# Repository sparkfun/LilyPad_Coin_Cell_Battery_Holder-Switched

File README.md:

SparkFun LilyPad Coin Cell Battery Holder-Switched
========================================

[*SparkFun LilyPad Coin Cell Battery Holder-Switched (DEV-11285)*](https://www.sparkfun.com/products/11285)

This LilyPad Coin Cell Battery Holder has a small slide switch installed on the board, 
in-line with the power so you can shut off your project and save batteries.

Repository Contents
-------------------
* **/Hardware** - All Eagle design files (.brd, .sch)

License Information
-------------------
The hardware is released under [Creative Commons ShareAlike 4.0 International](https://creativecommons.org/licenses/by-sa/4.0/).
Note: A portion of this sale is given back to Dr. Leah Buechley for continued development and education of e-textiles.

Distributed as-is; no warranty is given.

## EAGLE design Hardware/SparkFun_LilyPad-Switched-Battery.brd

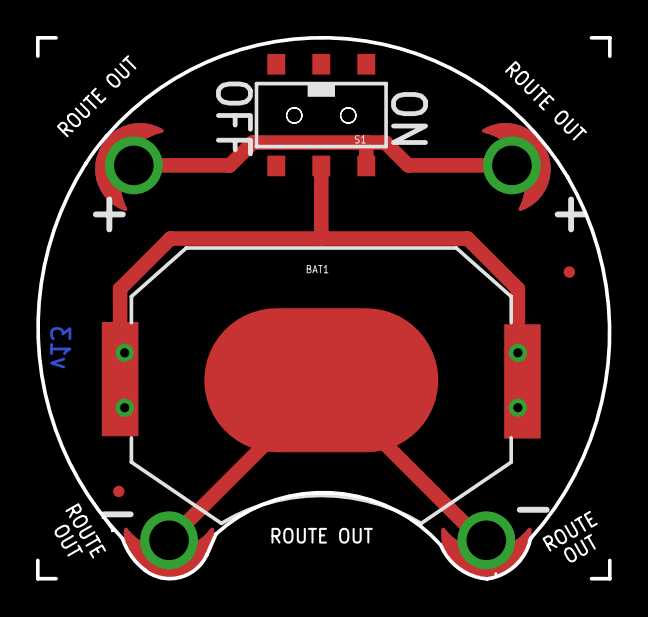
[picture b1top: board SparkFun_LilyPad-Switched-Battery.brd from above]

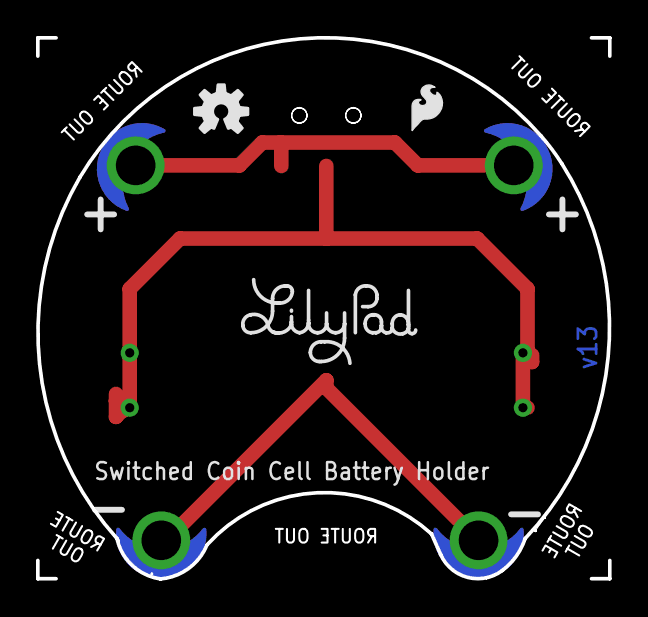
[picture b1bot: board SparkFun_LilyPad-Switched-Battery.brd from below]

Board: 2 copper layers, 31.8 x 30.1 mm, 13 parts (3 on the bottom side), 3 nets.

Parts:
BAT1: 20mm coincell; BATTCON_20MM_4LEGS
BATB-, BATB-2: SEWTAP6; PETAL-SMALL-2SIDE
BATT+, BATT+2: SEWTAP6; PETAL-SMALL-2SIDE
FD1, FD2: FIDUCIALUFIDUCIAL; MICRO-FIDUCIAL
FRAME1: FRAME-LETTER; CREATIVE_COMMONS
LOGO1: SFE_LOGO_FLAME.1_INCH; SFE_LOGO_FLAME_.1
LOGO2: OSHW-LOGOS; OSHW-LOGO-S
S1: AYZ0202
U$1: REVISION
U$3: LOGO-LILYPAD

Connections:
GND: BAT1.NEGATIVE, BATB-.1, BATB-2.1
unnamed: BAT1.POSITIVE@1, BAT1.POSITIVE@2, BAT1.POSITIVE@3, BAT1.POSITIVE@4, S1.2
unnamed: BATT+.1, BATT+2.1, S1.1

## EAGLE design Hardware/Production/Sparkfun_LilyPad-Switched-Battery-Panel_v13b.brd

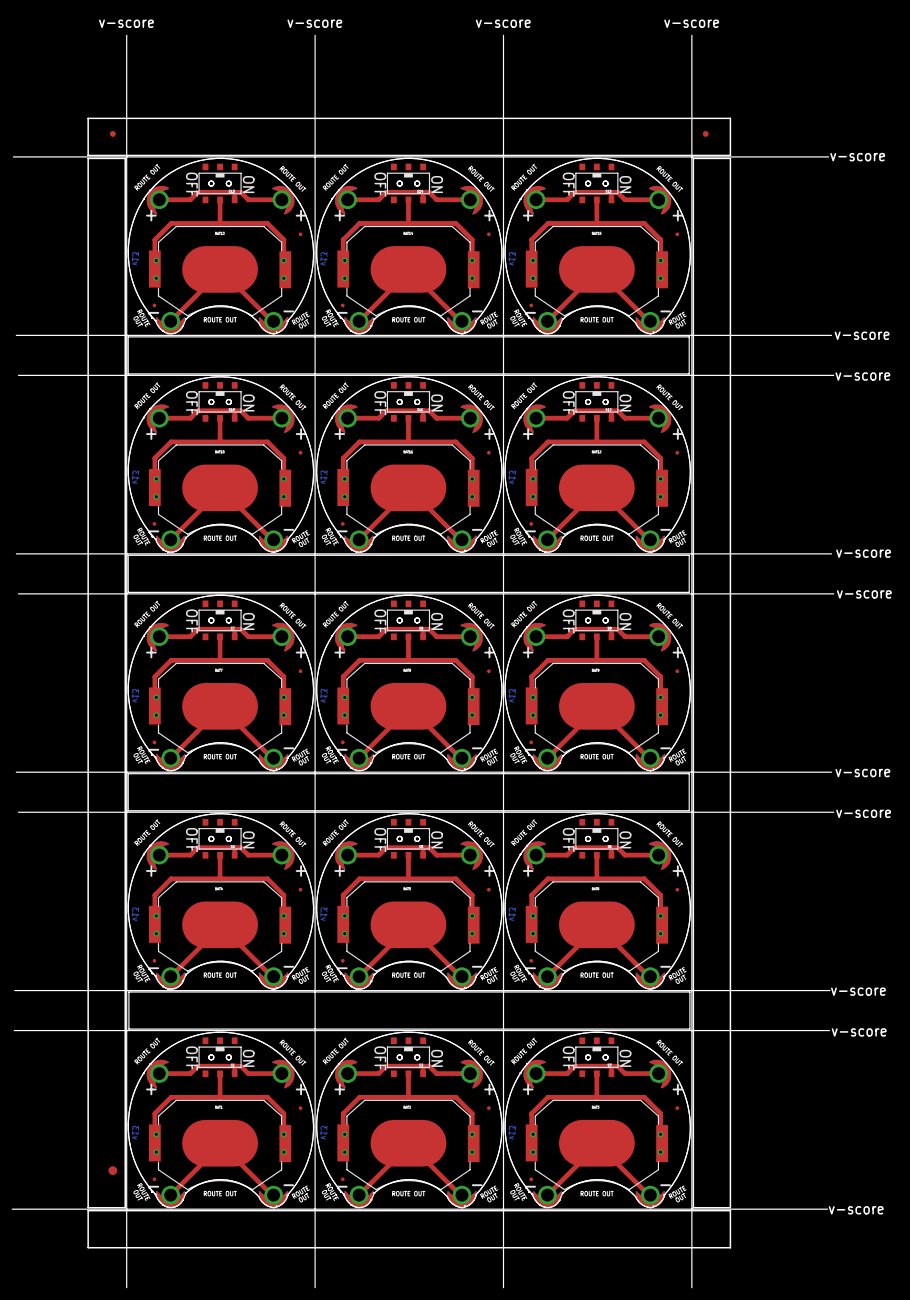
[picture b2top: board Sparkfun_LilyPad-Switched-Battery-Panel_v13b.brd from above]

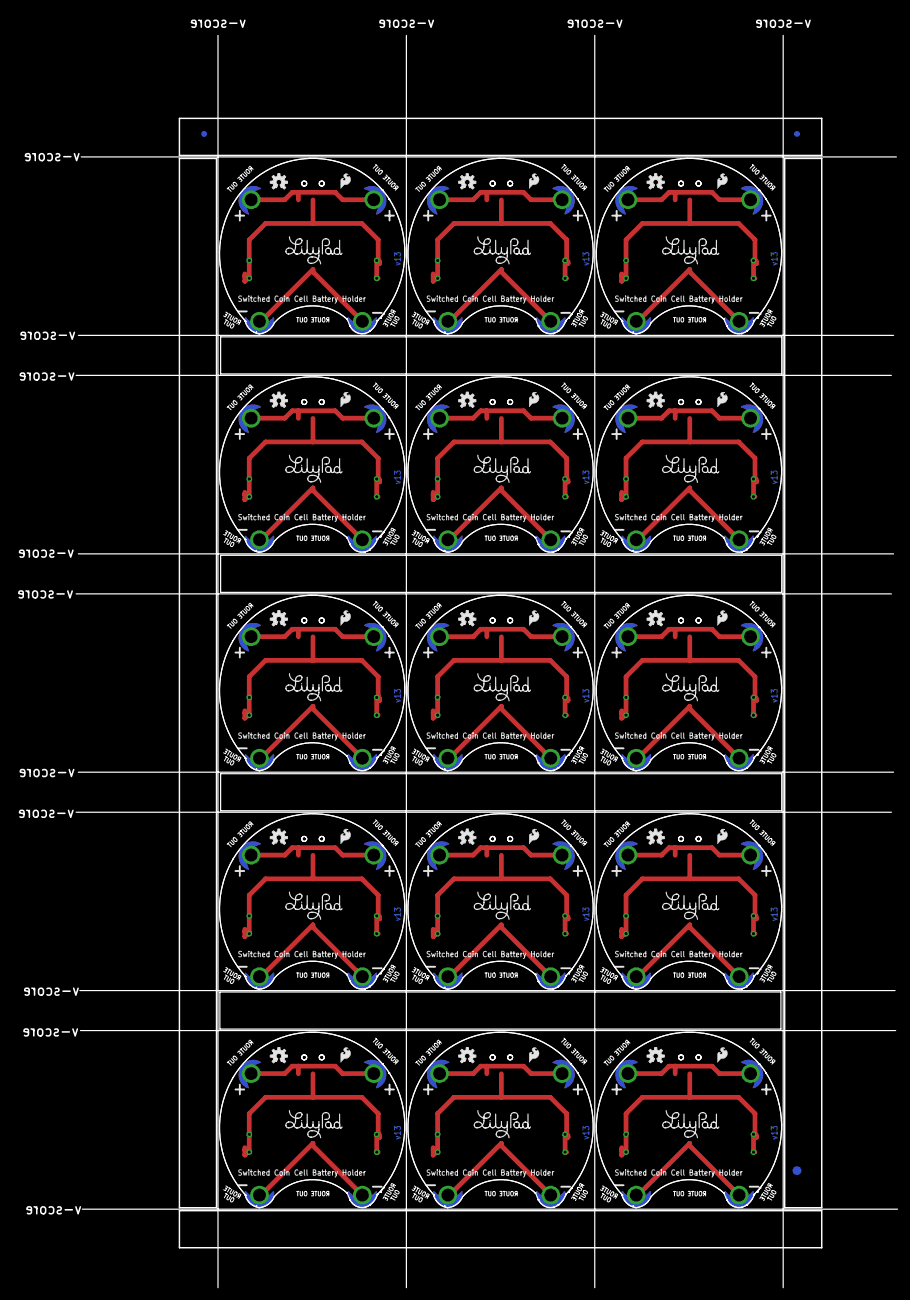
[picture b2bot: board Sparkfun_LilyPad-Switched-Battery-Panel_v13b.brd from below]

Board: 2 copper layers, 151.7 x 218.5 mm, 183 parts (48 on the bottom side), 45 nets.

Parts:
BAT1, BAT2, BAT3, BAT4, BAT5, BAT6, BAT7, BAT8, BAT9, BAT10, BAT11, BAT12, BAT13, BAT14, BAT15: 20mm coincell; BATTCON_20MM_4LEGS
BATB-, BATB-1, BATB-2, BATB-3, BATB-4, BATB-5, BATB-6, BATB-7, BATB-8, BATB-9, BATB-10, BATB-11, BATB-12, BATB-13, BATB-14, BATB-15, BATB-16, BATB-17, BATB-18, BATB-19, BATB-20, BATB-21, BATB-22, BATB-23, BATB-24, BATB-25, BATB-26, BATB-27, BATB-28, BATB-29: SEWTAP6; PETAL-SMALL-2SIDE
BATT+, BATT+1, BATT+2, BATT+3, BATT+4, BATT+5, BATT+6, BATT+7, BATT+8, BATT+9, BATT+10, BATT+11, BATT+12, BATT+13, BATT+14, BATT+15, BATT+16, BATT+17, BATT+18, BATT+19, BATT+20, BATT+21, BATT+22, BATT+23, BATT+24, BATT+25, BATT+26, BATT+27, BATT+28, BATT+29: SEWTAP6; PETAL-SMALL-2SIDE
E$1, E$2, E$3, E$4: FIDUCIAL-1X2
E$5, E$6: FIDUCIAL-1.5X3
FD1, FD2, FD3, FD4, FD5, FD6, FD7, FD8, FD9, FD10, FD11, FD12, FD13, FD14, FD15, FD16, FD17, FD18, FD19, FD20, FD21, FD22, FD23, FD24, FD25, FD26, FD27, FD28, FD29, FD30: FIDUCIALUFIDUCIAL; MICRO-FIDUCIAL
LOGO1, LOGO3, LOGO5, LOGO7, LOGO9, LOGO11, LOGO13, LOGO15, LOGO17, LOGO19, LOGO21, LOGO23, LOGO25, LOGO27, LOGO29: SFE_LOGO_FLAME.1_INCH; SFE_LOGO_FLAME_.1
LOGO2, LOGO4, LOGO6, LOGO8, LOGO10, LOGO12, LOGO14, LOGO16, LOGO18, LOGO20, LOGO22, LOGO24, LOGO26, LOGO28, LOGO30: OSHW-LOGOS; OSHW-LOGO-S
S1, S2, S3, S4, S5, S6, S7, S8, S9, S10, S11, S12, S13, S14, S15: AYZ0202
U$3, U$4, U$6, U$8, U$10, U$12, U$14, U$16, U$18, U$20, U$22, U$24, U$26, U$28, U$30: LOGO-LILYPAD
U$7, U$9, U$11, U$13, U$15, U$17, U$19, U$21, U$23, U$25, U$27, U$29: REVISION

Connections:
GND: BAT1.NEGATIVE, BATB-.1, BATB-2.1
GND1: BAT2.NEGATIVE, BATB-1.1, BATB-3.1
GND2: BAT3.NEGATIVE, BATB-4.1, BATB-5.1
GND3: BAT4.NEGATIVE, BATB-6.1, BATB-7.1
GND4: BAT5.NEGATIVE, BATB-8.1, BATB-9.1
GND5: BAT6.NEGATIVE, BATB-10.1, BATB-11.1
GND6: BAT7.NEGATIVE, BATB-12.1, BATB-13.1
GND7: BAT8.NEGATIVE, BATB-14.1, BATB-15.1
GND8: BAT9.NEGATIVE, BATB-16.1, BATB-17.1
GND9: BAT10.NEGATIVE, BATB-18.1, BATB-19.1
GND10: BAT11.NEGATIVE, BATB-20.1, BATB-21.1
GND11: BAT12.NEGATIVE, BATB-22.1, BATB-23.1
GND12: BAT13.NEGATIVE, BATB-24.1, BATB-25.1
GND13: BAT14.NEGATIVE, BATB-26.1, BATB-27.1
GND14: BAT15.NEGATIVE, BATB-28.1, BATB-29.1
unnamed: BAT1.POSITIVE@1, BAT1.POSITIVE@2, BAT1.POSITIVE@3, BAT1.POSITIVE@4, S1.2
unnamed: BATT+.1, BATT+2.1, S1.1
unnamed: BAT2.POSITIVE@1, BAT2.POSITIVE@2, BAT2.POSITIVE@3, BAT2.POSITIVE@4, S2.2
unnamed: BATT+1.1, BATT+3.1, S2.1
unnamed: BAT3.POSITIVE@1, BAT3.POSITIVE@2, BAT3.POSITIVE@3, BAT3.POSITIVE@4, S3.2
unnamed: BATT+4.1, BATT+5.1, S3.1
unnamed: BAT4.POSITIVE@1, BAT4.POSITIVE@2, BAT4.POSITIVE@3, BAT4.POSITIVE@4, S4.2
unnamed: BATT+6.1, BATT+7.1, S4.1
unnamed: BAT5.POSITIVE@1, BAT5.POSITIVE@2, BAT5.POSITIVE@3, BAT5.POSITIVE@4, S5.2
unnamed: BATT+8.1, BATT+9.1, S5.1
unnamed: BAT6.POSITIVE@1, BAT6.POSITIVE@2, BAT6.POSITIVE@3, BAT6.POSITIVE@4, S6.2
unnamed: BATT+10.1, BATT+11.1, S6.1
unnamed: BAT7.POSITIVE@1, BAT7.POSITIVE@2, BAT7.POSITIVE@3, BAT7.POSITIVE@4, S7.2
unnamed: BATT+12.1, BATT+13.1, S7.1
unnamed: BAT8.POSITIVE@1, BAT8.POSITIVE@2, BAT8.POSITIVE@3, BAT8.POSITIVE@4, S8.2
unnamed: BATT+14.1, BATT+15.1, S8.1
unnamed: BAT9.POSITIVE@1, BAT9.POSITIVE@2, BAT9.POSITIVE@3, BAT9.POSITIVE@4, S9.2
unnamed: BATT+16.1, BATT+17.1, S9.1
unnamed: BAT10.POSITIVE@1, BAT10.POSITIVE@2, BAT10.POSITIVE@3, BAT10.POSITIVE@4, S10.2
unnamed: BATT+18.1, BATT+19.1, S10.1
unnamed: BAT11.POSITIVE@1, BAT11.POSITIVE@2, BAT11.POSITIVE@3, BAT11.POSITIVE@4, S11.2
unnamed: BATT+20.1, BATT+21.1, S11.1
unnamed: BAT12.POSITIVE@1, BAT12.POSITIVE@2, BAT12.POSITIVE@3, BAT12.POSITIVE@4, S12.2
unnamed: BATT+22.1, BATT+23.1, S12.1
unnamed: BAT13.POSITIVE@1, BAT13.POSITIVE@2, BAT13.POSITIVE@3, BAT13.POSITIVE@4, S13.2
unnamed: BATT+24.1, BATT+25.1, S13.1
unnamed: BAT14.POSITIVE@1, BAT14.POSITIVE@2, BAT14.POSITIVE@3, BAT14.POSITIVE@4, S14.2
unnamed: BATT+26.1, BATT+27.1, S14.1
unnamed: BAT15.POSITIVE@1, BAT15.POSITIVE@2, BAT15.POSITIVE@3, BAT15.POSITIVE@4, S15.2
unnamed: BATT+28.1, BATT+29.1, S15.1

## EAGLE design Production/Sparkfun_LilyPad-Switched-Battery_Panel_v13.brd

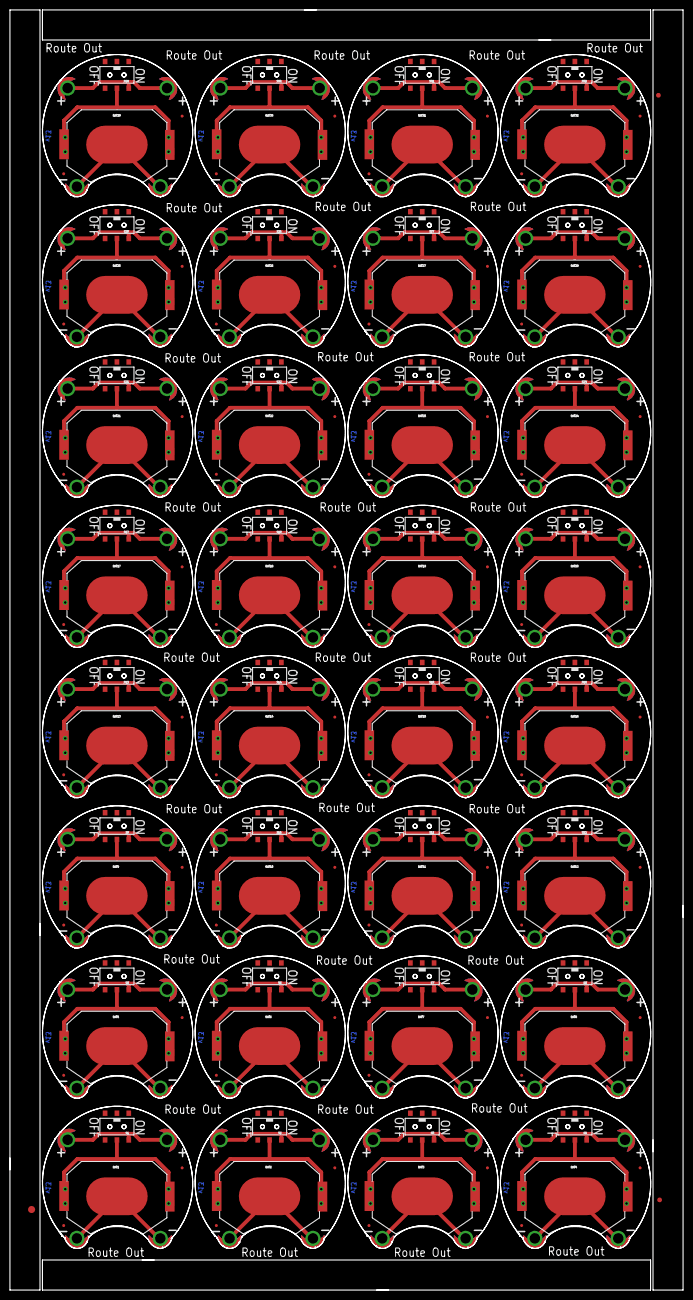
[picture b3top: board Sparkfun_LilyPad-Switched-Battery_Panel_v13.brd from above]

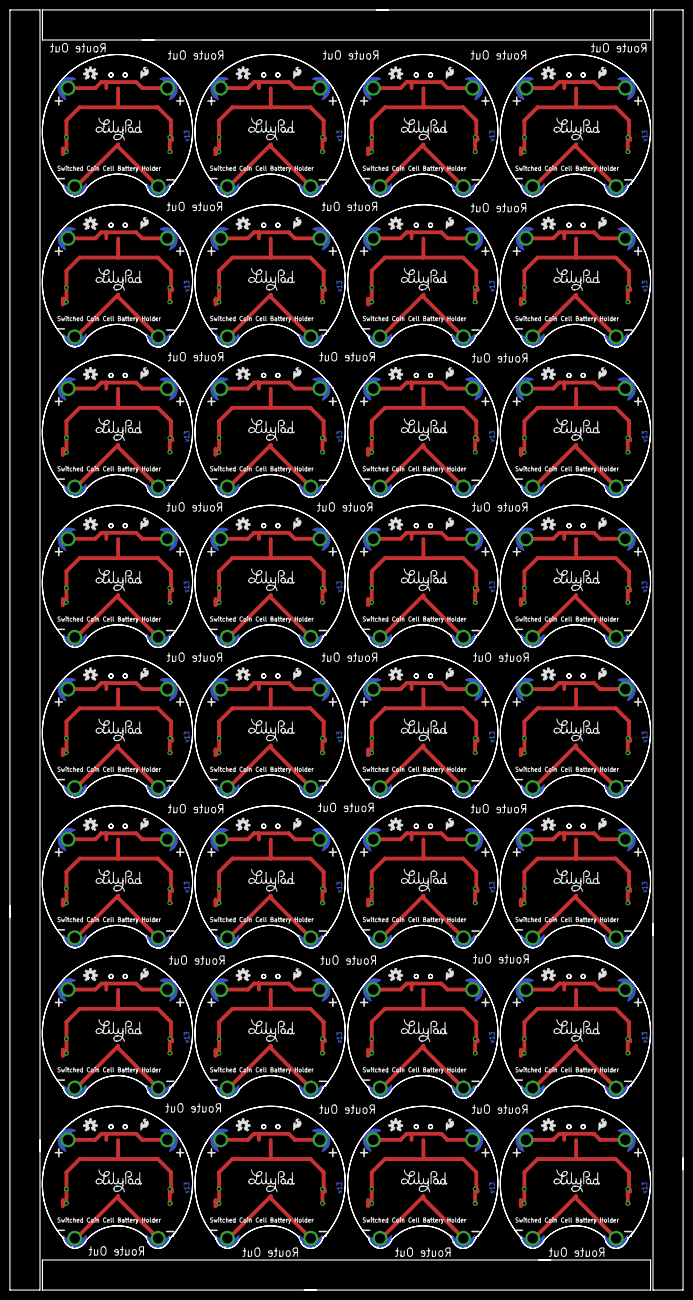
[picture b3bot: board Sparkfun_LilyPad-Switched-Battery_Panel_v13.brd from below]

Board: 2 copper layers, 142.2 x 270.5 mm, 355 parts (96 on the bottom side), 96 nets.

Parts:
BAT1, BAT2, BAT3, BAT4, BAT5, BAT6, BAT7, BAT8, BAT9, BAT10, BAT11, BAT12, BAT13, BAT14, BAT15, BAT16, BAT17, BAT18, BAT19, BAT20, BAT21, BAT22, BAT23, BAT24, BAT25, BAT26, BAT27, BAT28, BAT29, BAT30, BAT31, BAT32: 20mm coincell; BATTCON_20MM_4LEGS
BATB-, BATB-1, BATB-2, BATB-3, BATB-4, BATB-5, BATB-6, BATB-7, BATB-8, BATB-9, BATB-10, BATB-11, BATB-12, BATB-13, BATB-14, BATB-15, BATB-16, BATB-17, BATB-18, BATB-19, BATB-20, BATB-21, BATB-22, BATB-23, BATB-24, BATB-25, BATB-26, BATB-27, BATB-28, BATB-29, BATB-30, BATB-31, BATB-32, BATB-33, BATB-34, BATB-35, BATB-36, BATB-37, BATB-38, BATB-39, BATB-40, BATB-41, BATB-42, BATB-43, BATB-44, BATB-45, BATB-46, BATB-47, BATB-48, BATB-49, BATB-50, BATB-51, BATB-52, BATB-53, BATB-54, BATB-55, BATB-56, BATB-57, BATB-58, BATB-59, BATB-60, BATB-61, BATB-62, BATB-63: SEWTAP6; PETAL-SMALL-2SIDE
BATT+, BATT+1, BATT+2, BATT+3, BATT+4, BATT+5, BATT+6, BATT+7, BATT+8, BATT+9, BATT+10, BATT+11, BATT+12, BATT+13, BATT+14, BATT+15, BATT+16, BATT+17, BATT+18, BATT+19, BATT+20, BATT+21, BATT+22, BATT+23, BATT+24, BATT+25, BATT+26, BATT+27, BATT+28, BATT+29, BATT+30, BATT+31, BATT+32, BATT+33, BATT+34, BATT+35, BATT+36, BATT+37, BATT+38, BATT+39, BATT+40, BATT+41, BATT+42, BATT+43, BATT+44, BATT+45, BATT+46, BATT+47, BATT+48, BATT+49, BATT+50, BATT+51, BATT+52, BATT+53, BATT+54, BATT+55, BATT+56, BATT+57, BATT+58, BATT+59, BATT+60, BATT+61, BATT+62, BATT+63: SEWTAP6; PETAL-SMALL-2SIDE
E$1: FIDUCIAL-1.5X3
E$5, E$6: FIDUCIAL-1X2
FD1, FD2, FD3, FD4, FD5, FD6, FD7, FD8, FD9, FD10, FD11, FD12, FD13, FD14, FD15, FD16, FD17, FD18, FD19, FD20, FD21, FD22, FD23, FD24, FD25, FD26, FD27, FD28, FD29, FD30, FD31, FD32, FD33, FD34, FD35, FD36, FD37, FD38, FD39, FD40, FD41, FD42, FD43, FD44, FD45, FD46, FD47, FD48, FD49, FD50, FD51, FD52, FD53, FD54, FD55, FD56, FD57, FD58, FD59, FD60, FD61, FD62, FD63, FD64: FIDUCIALUFIDUCIAL; MICRO-FIDUCIAL
LOGO1, LOGO3, LOGO5, LOGO7, LOGO9, LOGO11, LOGO13, LOGO15, LOGO17, LOGO19, LOGO21, LOGO23, LOGO25, LOGO27, LOGO29, LOGO31, LOGO33, LOGO35, LOGO37, LOGO39, LOGO41, LOGO43, LOGO45, LOGO47, LOGO49, LOGO51, LOGO53, LOGO55, LOGO57, LOGO59, LOGO61, LOGO63: SFE_LOGO_FLAME.1_INCH; SFE_LOGO_FLAME_.1
LOGO2, LOGO4, LOGO6, LOGO8, LOGO10, LOGO12, LOGO14, LOGO16, LOGO18, LOGO20, LOGO22, LOGO24, LOGO26, LOGO28, LOGO30, LOGO32, LOGO34, LOGO36, LOGO38, LOGO40, LOGO42, LOGO44, LOGO46, LOGO48, LOGO50, LOGO52, LOGO54, LOGO56, LOGO58, LOGO60, LOGO62, LOGO64: OSHW-LOGOS; OSHW-LOGO-S
S1, S2, S3, S4, S5, S6, S7, S8, S9, S10, S11, S12, S13, S14, S15, S16, S17, S18, S19, S20, S21, S22, S23, S24, S25, S26, S27, S28, S29, S30, S31, S32: AYZ0202
U$1, U$2, U$3, U$4, U$5, U$6, U$7, U$8, U$9, U$10, U$11, U$12, U$13, U$14, U$15, U$16, U$17, U$18, U$19, U$20, U$21, U$22, U$23, U$24, U$25, U$26, U$27, U$28, U$29, U$30, U$31, U$32: LOGO-LILYPAD

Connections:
GND: BAT1.NEGATIVE, BATB-.1, BATB-2.1
GND1: BAT2.NEGATIVE, BATB-1.1, BATB-3.1
GND2: BAT3.NEGATIVE, BATB-4.1, BATB-5.1
GND3: BAT4.NEGATIVE, BATB-6.1, BATB-7.1
GND4: BAT5.NEGATIVE, BATB-8.1, BATB-9.1
GND5: BAT6.NEGATIVE, BATB-10.1, BATB-11.1
GND6: BAT7.NEGATIVE, BATB-12.1, BATB-13.1
GND7: BAT8.NEGATIVE, BATB-14.1, BATB-15.1
GND8: BAT9.NEGATIVE, BATB-16.1, BATB-17.1
GND9: BAT10.NEGATIVE, BATB-18.1, BATB-19.1
GND10: BAT11.NEGATIVE, BATB-20.1, BATB-21.1
GND11: BAT12.NEGATIVE, BATB-22.1, BATB-23.1
GND12: BAT13.NEGATIVE, BATB-24.1, BATB-25.1
GND13: BAT14.NEGATIVE, BATB-26.1, BATB-27.1
GND14: BAT15.NEGATIVE, BATB-28.1, BATB-29.1
GND15: BAT16.NEGATIVE, BATB-30.1, BATB-31.1
GND16: BAT17.NEGATIVE, BATB-32.1, BATB-33.1
GND17: BAT18.NEGATIVE, BATB-34.1, BATB-35.1
GND18: BAT19.NEGATIVE, BATB-36.1, BATB-37.1
GND19: BAT20.NEGATIVE, BATB-38.1, BATB-39.1
GND20: BAT21.NEGATIVE, BATB-40.1, BATB-41.1
GND21: BAT22.NEGATIVE, BATB-42.1, BATB-43.1
GND22: BAT23.NEGATIVE, BATB-44.1, BATB-45.1
GND23: BAT24.NEGATIVE, BATB-46.1, BATB-47.1
GND24: BAT25.NEGATIVE, BATB-48.1, BATB-49.1
GND25: BAT26.NEGATIVE, BATB-50.1, BATB-51.1
GND26: BAT27.NEGATIVE, BATB-52.1, BATB-53.1
GND27: BAT28.NEGATIVE, BATB-54.1, BATB-55.1
GND28: BAT29.NEGATIVE, BATB-56.1, BATB-57.1
GND29: BAT30.NEGATIVE, BATB-58.1, BATB-59.1
GND30: BAT31.NEGATIVE, BATB-60.1, BATB-61.1
GND31: BAT32.NEGATIVE, BATB-62.1, BATB-63.1
unnamed: BAT1.POSITIVE@1, BAT1.POSITIVE@2, BAT1.POSITIVE@3, BAT1.POSITIVE@4, S1.2
unnamed: BATT+.1, BATT+2.1, S1.1
unnamed: BAT2.POSITIVE@1, BAT2.POSITIVE@2, BAT2.POSITIVE@3, BAT2.POSITIVE@4, S2.2
unnamed: BATT+1.1, BATT+3.1, S2.1
unnamed: BAT3.POSITIVE@1, BAT3.POSITIVE@2, BAT3.POSITIVE@3, BAT3.POSITIVE@4, S3.2
unnamed: BATT+4.1, BATT+5.1, S3.1
unnamed: BAT4.POSITIVE@1, BAT4.POSITIVE@2, BAT4.POSITIVE@3, BAT4.POSITIVE@4, S4.2
unnamed: BATT+6.1, BATT+7.1, S4.1
unnamed: BAT5.POSITIVE@1, BAT5.POSITIVE@2, BAT5.POSITIVE@3, BAT5.POSITIVE@4, S5.2
unnamed: BATT+8.1, BATT+9.1, S5.1
unnamed: BAT6.POSITIVE@1, BAT6.POSITIVE@2, BAT6.POSITIVE@3, BAT6.POSITIVE@4, S6.2
unnamed: BATT+10.1, BATT+11.1, S6.1
unnamed: BAT7.POSITIVE@1, BAT7.POSITIVE@2, BAT7.POSITIVE@3, BAT7.POSITIVE@4, S7.2
unnamed: BATT+12.1, BATT+13.1, S7.1
unnamed: BAT8.POSITIVE@1, BAT8.POSITIVE@2, BAT8.POSITIVE@3, BAT8.POSITIVE@4, S8.2
unnamed: BATT+14.1, BATT+15.1, S8.1
unnamed: BAT9.POSITIVE@1, BAT9.POSITIVE@2, BAT9.POSITIVE@3, BAT9.POSITIVE@4, S9.2
unnamed: BATT+16.1, BATT+17.1, S9.1
unnamed: BAT10.POSITIVE@1, BAT10.POSITIVE@2, BAT10.POSITIVE@3, BAT10.POSITIVE@4, S10.2
unnamed: BATT+18.1, BATT+19.1, S10.1
unnamed: BAT11.POSITIVE@1, BAT11.POSITIVE@2, BAT11.POSITIVE@3, BAT11.POSITIVE@4, S11.2
unnamed: BATT+20.1, BATT+21.1, S11.1
unnamed: BAT12.POSITIVE@1, BAT12.POSITIVE@2, BAT12.POSITIVE@3, BAT12.POSITIVE@4, S12.2
unnamed: BATT+22.1, BATT+23.1, S12.1
unnamed: BAT13.POSITIVE@1, BAT13.POSITIVE@2, BAT13.POSITIVE@3, BAT13.POSITIVE@4, S13.2
unnamed: BATT+24.1, BATT+25.1, S13.1
unnamed: BAT14.POSITIVE@1, BAT14.POSITIVE@2, BAT14.POSITIVE@3, BAT14.POSITIVE@4, S14.2
unnamed: BATT+26.1, BATT+27.1, S14.1
unnamed: BAT15.POSITIVE@1, BAT15.POSITIVE@2, BAT15.POSITIVE@3, BAT15.POSITIVE@4, S15.2
unnamed: BATT+28.1, BATT+29.1, S15.1
unnamed: BAT16.POSITIVE@1, BAT16.POSITIVE@2, BAT16.POSITIVE@3, BAT16.POSITIVE@4, S16.2
unnamed: BATT+30.1, BATT+31.1, S16.1
unnamed: BAT17.POSITIVE@1, BAT17.POSITIVE@2, BAT17.POSITIVE@3, BAT17.POSITIVE@4, S17.2
unnamed: BATT+32.1, BATT+33.1, S17.1
unnamed: BAT18.POSITIVE@1, BAT18.POSITIVE@2, BAT18.POSITIVE@3, BAT18.POSITIVE@4, S18.2
unnamed: BATT+34.1, BATT+35.1, S18.1
unnamed: BAT19.POSITIVE@1, BAT19.POSITIVE@2, BAT19.POSITIVE@3, BAT19.POSITIVE@4, S19.2
unnamed: BATT+36.1, BATT+37.1, S19.1
unnamed: BAT20.POSITIVE@1, BAT20.POSITIVE@2, BAT20.POSITIVE@3, BAT20.POSITIVE@4, S20.2
unnamed: BATT+38.1, BATT+39.1, S20.1
unnamed: BAT21.POSITIVE@1, BAT21.POSITIVE@2, BAT21.POSITIVE@3, BAT21.POSITIVE@4, S21.2
unnamed: BATT+40.1, BATT+41.1, S21.1
unnamed: BAT22.POSITIVE@1, BAT22.POSITIVE@2, BAT22.POSITIVE@3, BAT22.POSITIVE@4, S22.2
unnamed: BATT+42.1, BATT+43.1, S22.1
unnamed: BAT23.POSITIVE@1, BAT23.POSITIVE@2, BAT23.POSITIVE@3, BAT23.POSITIVE@4, S23.2
unnamed: BATT+44.1, BATT+45.1, S23.1
unnamed: BAT24.POSITIVE@1, BAT24.POSITIVE@2, BAT24.POSITIVE@3, BAT24.POSITIVE@4, S24.2
unnamed: BATT+46.1, BATT+47.1, S24.1
unnamed: BAT25.POSITIVE@1, BAT25.POSITIVE@2, BAT25.POSITIVE@3, BAT25.POSITIVE@4, S25.2
unnamed: BATT+48.1, BATT+49.1, S25.1
unnamed: BAT26.POSITIVE@1, BAT26.POSITIVE@2, BAT26.POSITIVE@3, BAT26.POSITIVE@4, S26.2
unnamed: BATT+50.1, BATT+51.1, S26.1
unnamed: BAT27.POSITIVE@1, BAT27.POSITIVE@2, BAT27.POSITIVE@3, BAT27.POSITIVE@4, S27.2
unnamed: BATT+52.1, BATT+53.1, S27.1
unnamed: BAT28.POSITIVE@1, BAT28.POSITIVE@2, BAT28.POSITIVE@3, BAT28.POSITIVE@4, S28.2
unnamed: BATT+54.1, BATT+55.1, S28.1
unnamed: BAT29.POSITIVE@1, BAT29.POSITIVE@2, BAT29.POSITIVE@3, BAT29.POSITIVE@4, S29.2
unnamed: BATT+56.1, BATT+57.1, S29.1
unnamed: BAT30.POSITIVE@1, BAT30.POSITIVE@2, BAT30.POSITIVE@3, BAT30.POSITIVE@4, S30.2
unnamed: BATT+58.1, BATT+59.1, S30.1
unnamed: BAT31.POSITIVE@1, BAT31.POSITIVE@2, BAT31.POSITIVE@3, BAT31.POSITIVE@4, S31.2
unnamed: BATT+60.1, BATT+61.1, S31.1
unnamed: BAT32.POSITIVE@1, BAT32.POSITIVE@2, BAT32.POSITIVE@3, BAT32.POSITIVE@4, S32.2
unnamed: BATT+62.1, BATT+63.1, S32.1

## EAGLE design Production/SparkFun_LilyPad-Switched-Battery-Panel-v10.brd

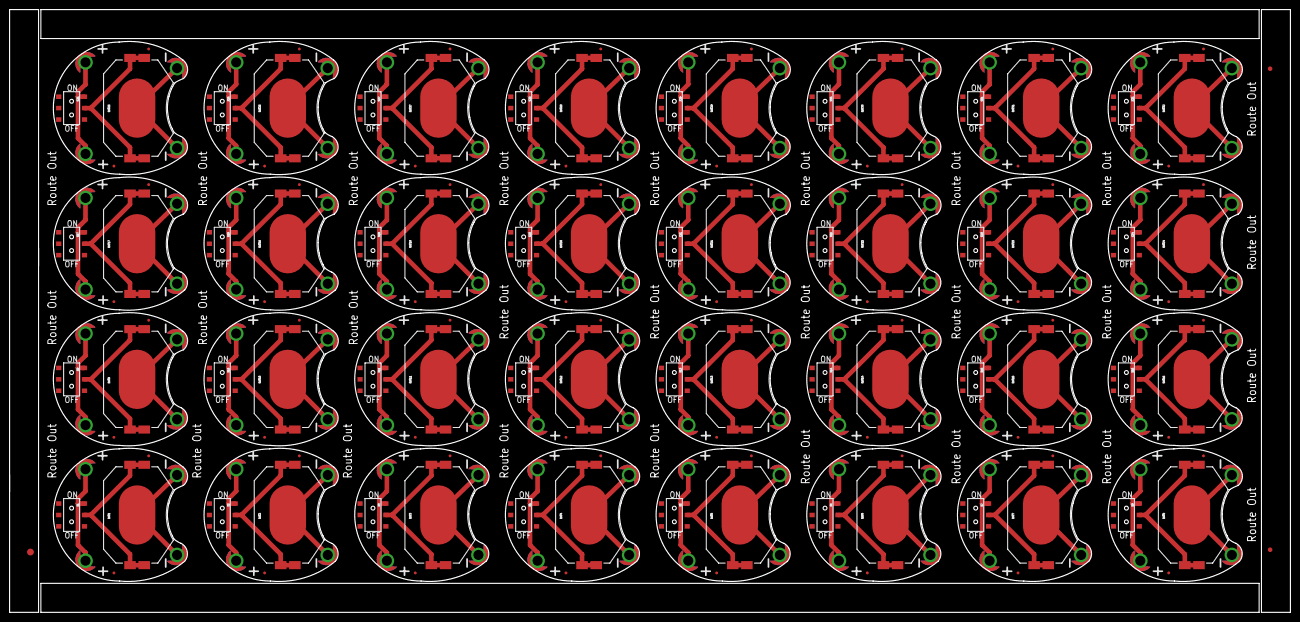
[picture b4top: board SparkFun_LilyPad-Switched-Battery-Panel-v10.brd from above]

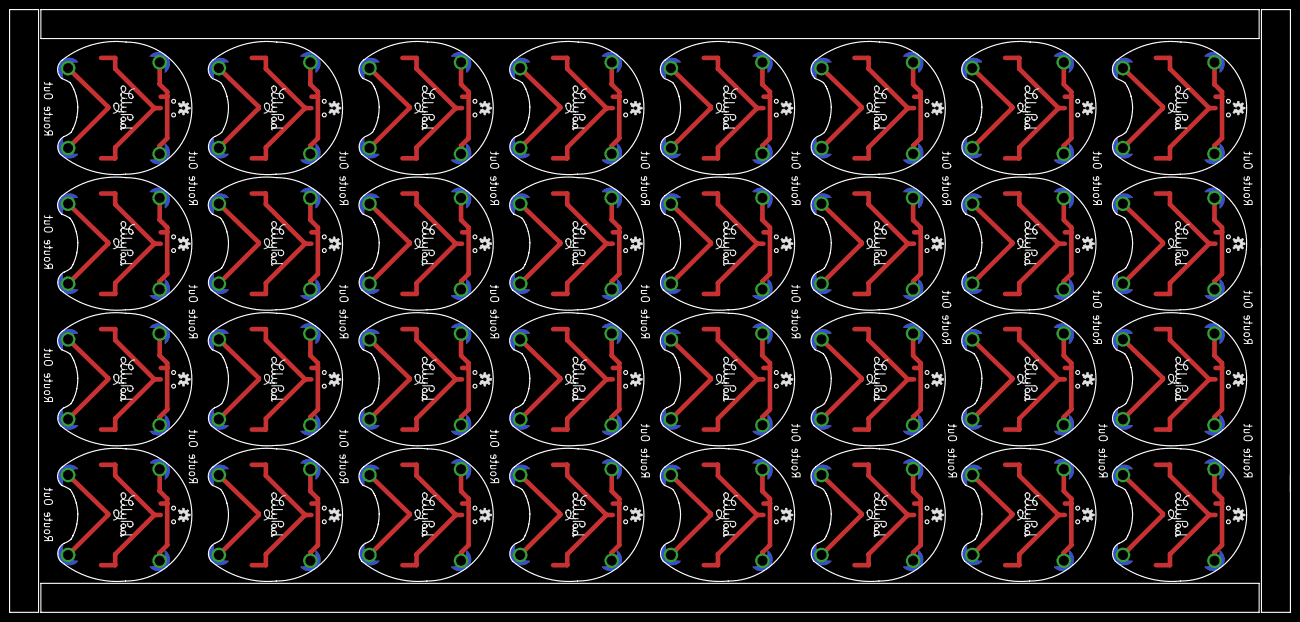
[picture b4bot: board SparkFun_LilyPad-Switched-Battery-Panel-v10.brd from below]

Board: 2 copper layers, 280.6 x 132.0 mm, 323 parts (64 on the bottom side), 96 nets.

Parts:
BAT1, BAT2, BAT3, BAT4, BAT5, BAT6, BAT7, BAT8, BAT9, BAT10, BAT11, BAT12, BAT13, BAT14, BAT15, BAT16, BAT17, BAT18, BAT19, BAT20, BAT21, BAT22, BAT23, BAT24, BAT25, BAT26, BAT27, BAT28, BAT29, BAT30, BAT31, BAT32: BATTCON_20MM_4LEGS
E$1: FIDUCIAL-1.5X3
E$5, E$6: FIDUCIAL-1X2
JP1, JP2, JP3, JP4, JP5, JP6, JP7, JP8, JP9, JP10, JP11, JP12, JP13, JP14, JP15, JP16, JP17, JP18, JP19, JP20, JP21, JP22, JP23, JP24, JP25, JP26, JP27, JP28, JP29, JP30, JP31, JP32, JP33, JP34, JP35, JP36, JP37, JP38, JP39, JP40, JP41, JP42, JP43, JP44, JP45, JP46, JP47, JP48, JP49, JP50, JP51, JP52, JP53, JP54, JP55, JP56, JP57, JP58, JP59, JP60, JP61, JP62, JP63, JP64: FIDUCIALUFIDUCIAL; MICRO-FIDUCIAL
S1, S2, S3, S4, S5, S6, S7, S8, S9, S10, S11, S12, S13, S14, S15, S16, S17, S18, S19, S20, S21, S22, S23, S24, S25, S26, S27, S28, S29, S30, S31, S32: AYZ0202
U$1, U$2, U$3, U$4, U$6, U$8, U$9, U$10, U$13, U$14, U$15, U$16, U$19, U$20, U$21, U$22, U$25, U$26, U$27, U$28, U$31, U$32, U$33, U$34, U$37, U$38, U$39, U$40, U$43, U$44, U$45, U$46, U$49, U$50, U$51, U$52, U$55, U$56, U$57, U$58, U$61, U$62, U$63, U$64, U$67, U$68, U$69, U$70, U$73, U$74, U$75, U$76, U$79, U$80, U$81, U$82, U$85, U$86, U$87, U$88, U$91, U$92, U$93, U$94, U$97, U$98, U$99, U$100, U$103, U$104, U$105, U$106, U$109, U$110, U$111, U$112, U$115, U$116, U$117, U$118, U$121, U$122, U$123, U$124, U$127, U$128, U$129, U$130, U$133, U$134, U$135, U$136, U$139, U$140, U$141, U$142, U$145, U$146, U$147, U$148, U$151, U$152, U$153, U$154, U$157, U$158, U$159, U$160, U$163, U$164, U$165, U$166, U$169, U$170, U$171, U$172, U$175, U$176, U$177, U$178, U$181, U$182, U$183, U$184, U$187, U$188, U$189, U$190: SEWTAP6; PETAL-SMALL-2SIDE
U$5, U$11, U$17, U$23, U$29, U$35, U$41, U$47, U$53, U$59, U$65, U$71, U$77, U$83, U$89, U$95, U$101, U$107, U$113, U$119, U$125, U$131, U$137, U$143, U$149, U$155, U$161, U$167, U$173, U$179, U$185, U$191: LOGO-LPLP; LOGO-LILYPAD
U$7, U$12, U$18, U$24, U$30, U$36, U$42, U$48, U$54, U$60, U$66, U$72, U$78, U$84, U$90, U$96, U$102, U$108, U$114, U$120, U$126, U$132, U$138, U$144, U$150, U$156, U$162, U$168, U$174, U$180, U$186, U$192: OSHW-LOGOS; OSHW-LOGO-S

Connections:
unnamed: S1.1, U$2.1, U$4.1
unnamed: BAT1.2, U$1.1, U$3.1
unnamed: BAT1.1, BAT1.3, BAT1.P$1, BAT1.P$2, S1.2
unnamed: BAT2.2, U$6.1, U$9.1
unnamed: S2.1, U$8.1, U$10.1
unnamed: BAT2.1, BAT2.3, BAT2.P$1, BAT2.P$2, S2.2
unnamed: BAT3.2, U$13.1, U$15.1
unnamed: S3.1, U$14.1, U$16.1
unnamed: BAT3.1, BAT3.3, BAT3.P$1, BAT3.P$2, S3.2
unnamed: BAT4.2, U$19.1, U$21.1
unnamed: S4.1, U$20.1, U$22.1
unnamed: BAT4.1, BAT4.3, BAT4.P$1, BAT4.P$2, S4.2
unnamed: BAT5.2, U$25.1, U$27.1
unnamed: S5.1, U$26.1, U$28.1
unnamed: BAT5.1, BAT5.3, BAT5.P$1, BAT5.P$2, S5.2
unnamed: BAT6.2, U$31.1, U$33.1
unnamed: S6.1, U$32.1, U$34.1
unnamed: BAT6.1, BAT6.3, BAT6.P$1, BAT6.P$2, S6.2
unnamed: BAT7.2, U$37.1, U$39.1
unnamed: S7.1, U$38.1, U$40.1
unnamed: BAT7.1, BAT7.3, BAT7.P$1, BAT7.P$2, S7.2
unnamed: BAT8.2, U$43.1, U$45.1
unnamed: S8.1, U$44.1, U$46.1
unnamed: BAT8.1, BAT8.3, BAT8.P$1, BAT8.P$2, S8.2
unnamed: BAT9.2, U$49.1, U$51.1
unnamed: S9.1, U$50.1, U$52.1
unnamed: BAT9.1, BAT9.3, BAT9.P$1, BAT9.P$2, S9.2
unnamed: BAT10.2, U$55.1, U$57.1
unnamed: S10.1, U$56.1, U$58.1
unnamed: BAT10.1, BAT10.3, BAT10.P$1, BAT10.P$2, S10.2
unnamed: BAT11.2, U$61.1, U$63.1
unnamed: S11.1, U$62.1, U$64.1
unnamed: BAT11.1, BAT11.3, BAT11.P$1, BAT11.P$2, S11.2
unnamed: BAT12.2, U$67.1, U$69.1
unnamed: S12.1, U$68.1, U$70.1
unnamed: BAT12.1, BAT12.3, BAT12.P$1, BAT12.P$2, S12.2
unnamed: BAT13.2, U$73.1, U$75.1
unnamed: S13.1, U$74.1, U$76.1
unnamed: BAT13.1, BAT13.3, BAT13.P$1, BAT13.P$2, S13.2
unnamed: BAT14.2, U$79.1, U$81.1
unnamed: S14.1, U$80.1, U$82.1
unnamed: BAT14.1, BAT14.3, BAT14.P$1, BAT14.P$2, S14.2
unnamed: BAT15.2, U$85.1, U$87.1
unnamed: S15.1, U$86.1, U$88.1
unnamed: BAT15.1, BAT15.3, BAT15.P$1, BAT15.P$2, S15.2
unnamed: BAT16.2, U$91.1, U$93.1
unnamed: S16.1, U$92.1, U$94.1
unnamed: BAT16.1, BAT16.3, BAT16.P$1, BAT16.P$2, S16.2
unnamed: BAT17.2, U$97.1, U$99.1
unnamed: S17.1, U$98.1, U$100.1
unnamed: BAT17.1, BAT17.3, BAT17.P$1, BAT17.P$2, S17.2
unnamed: BAT18.2, U$103.1, U$105.1
unnamed: S18.1, U$104.1, U$106.1
unnamed: BAT18.1, BAT18.3, BAT18.P$1, BAT18.P$2, S18.2
unnamed: BAT19.2, U$109.1, U$111.1
unnamed: S19.1, U$110.1, U$112.1
unnamed: BAT19.1, BAT19.3, BAT19.P$1, BAT19.P$2, S19.2
unnamed: BAT20.2, U$115.1, U$117.1
unnamed: S20.1, U$116.1, U$118.1
unnamed: BAT20.1, BAT20.3, BAT20.P$1, BAT20.P$2, S20.2
unnamed: BAT21.2, U$121.1, U$123.1
unnamed: S21.1, U$122.1, U$124.1
unnamed: BAT21.1, BAT21.3, BAT21.P$1, BAT21.P$2, S21.2
unnamed: BAT22.2, U$127.1, U$129.1
unnamed: S22.1, U$128.1, U$130.1
unnamed: BAT22.1, BAT22.3, BAT22.P$1, BAT22.P$2, S22.2
unnamed: BAT23.2, U$133.1, U$135.1
unnamed: S23.1, U$134.1, U$136.1
unnamed: BAT23.1, BAT23.3, BAT23.P$1, BAT23.P$2, S23.2
unnamed: BAT24.2, U$139.1, U$141.1
unnamed: S24.1, U$140.1, U$142.1
unnamed: BAT24.1, BAT24.3, BAT24.P$1, BAT24.P$2, S24.2
unnamed: BAT25.2, U$145.1, U$147.1
unnamed: S25.1, U$146.1, U$148.1
unnamed: BAT25.1, BAT25.3, BAT25.P$1, BAT25.P$2, S25.2
unnamed: BAT26.2, U$151.1, U$153.1
unnamed: S26.1, U$152.1, U$154.1
unnamed: BAT26.1, BAT26.3, BAT26.P$1, BAT26.P$2, S26.2
unnamed: BAT27.2, U$157.1, U$159.1
unnamed: S27.1, U$158.1, U$160.1
unnamed: BAT27.1, BAT27.3, BAT27.P$1, BAT27.P$2, S27.2
unnamed: BAT28.2, U$163.1, U$165.1
unnamed: S28.1, U$164.1, U$166.1
unnamed: BAT28.1, BAT28.3, BAT28.P$1, BAT28.P$2, S28.2
unnamed: BAT29.2, U$169.1, U$171.1
unnamed: S29.1, U$170.1, U$172.1
unnamed: BAT29.1, BAT29.3, BAT29.P$1, BAT29.P$2, S29.2
unnamed: BAT30.2, U$175.1, U$177.1
unnamed: S30.1, U$176.1, U$178.1
unnamed: BAT30.1, BAT30.3, BAT30.P$1, BAT30.P$2, S30.2
unnamed: BAT31.2, U$181.1, U$183.1
unnamed: S31.1, U$182.1, U$184.1
unnamed: BAT31.1, BAT31.3, BAT31.P$1, BAT31.P$2, S31.2
unnamed: BAT32.2, U$187.1, U$189.1
unnamed: S32.1, U$188.1, U$190.1
unnamed: BAT32.1, BAT32.3, BAT32.P$1, BAT32.P$2, S32.2

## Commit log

2015-02-05 Initial hardware commit
2015-08-10 created larger panel
2015-08-10 added "route out"
2016-03-24 updated board and sch files
2016-03-31 Updated Board and Schematic files
2016-03-31 Updated Board Files
2016-04-01 Updated Board and Schematic files per QC
2016-04-14 Updated Board file
2016-04-14 Updated Board file, added package variant for battery holder
2016-04-15 Updated Coin Cell Battery Holder
2016-06-09 Cleaning up Repo
2016-06-09 Updated Brd and Sch files
2016-06-10 Updated Brd files per Eng Design Review
2016-06-13 Updated Brd file per QC
2016-06-13 updated brd File - Approved DRC Errors
2016-06-13 Approved DRC errors
2016-06-13 Fixed errors in tdocu
2016-06-13 Fixed DRC errors
2016-06-15 created panel v13
2016-06-15 deleted old panel
2021-12-06 Add board thickness
2021-12-08 Panel v13b - added inner tabs
    Added inner tabs for more points of contact, which makes a stronger panel.
2021-12-08 resolving merge conflicts - again

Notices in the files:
parts and their libraries:
SparkFun-Electromechanical: Licensing: Creative Commons ShareAlike 4.0 International - https://creativecommons.org/licenses/by-sa/4.0
SparkFun-Aesthetics: Licensing: CC v3.0 Share-Alike You are welcome to use this library for commercial purposes.
